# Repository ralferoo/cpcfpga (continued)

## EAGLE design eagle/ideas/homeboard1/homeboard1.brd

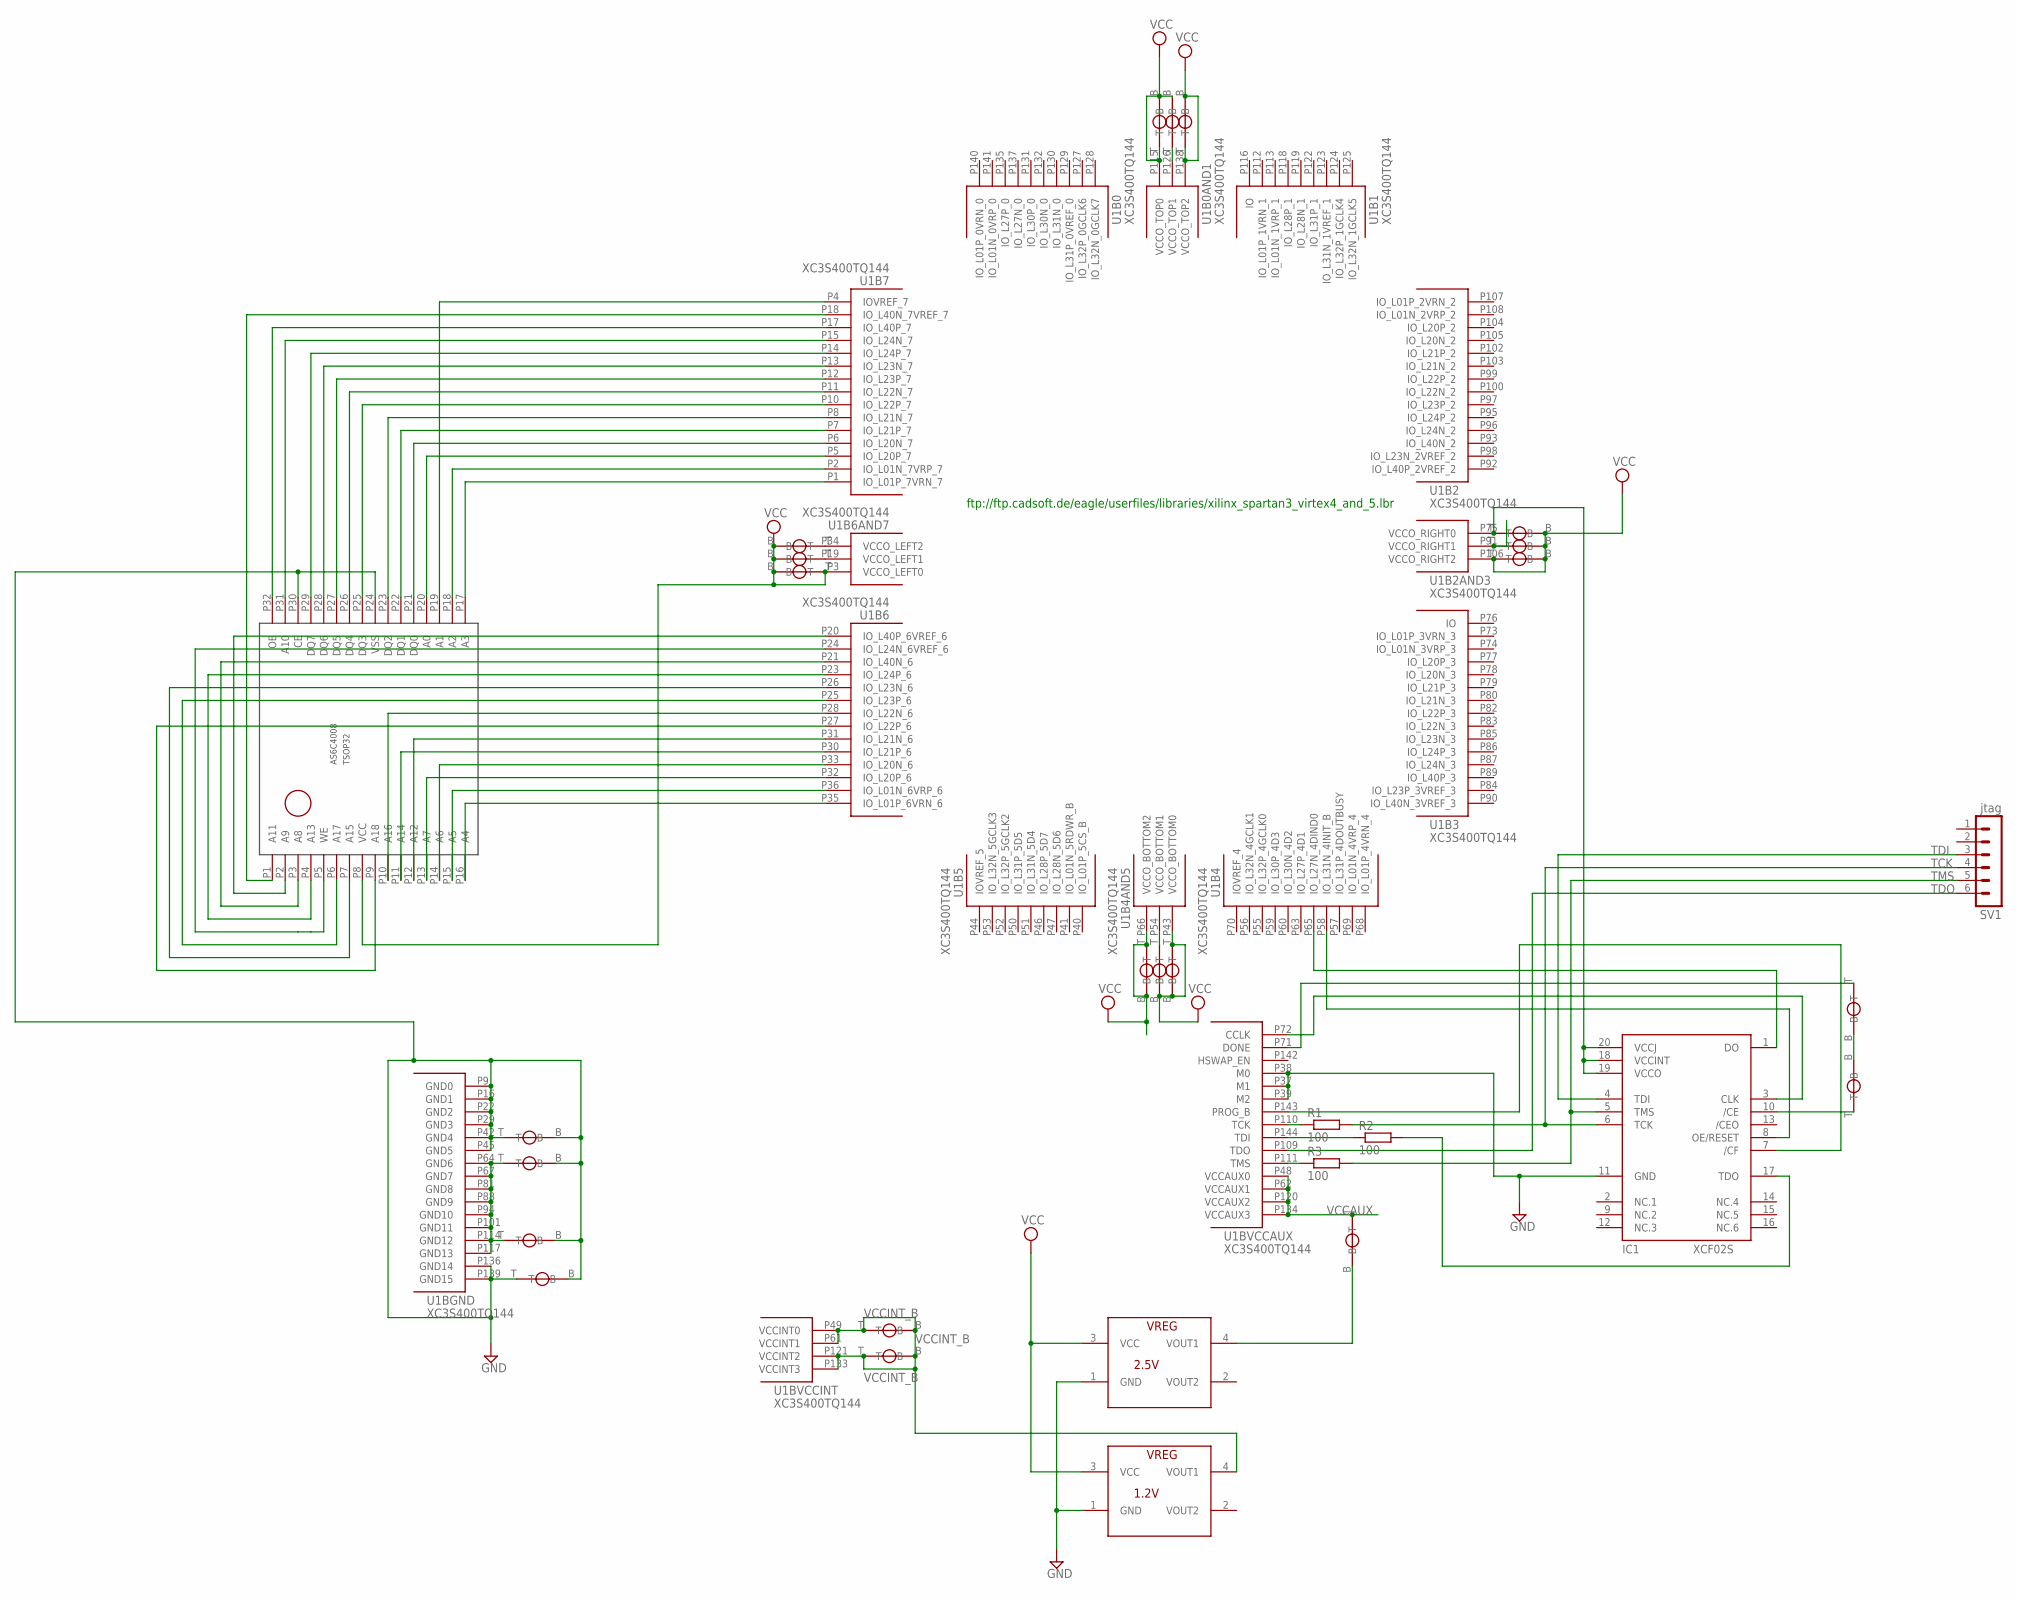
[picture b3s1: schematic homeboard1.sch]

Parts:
IC1: XCF02S; VO20
R1, R2, R3: 100; R0805
SV1: jtag; MA06-1
U1: XC3S400TQ144; TQ144
U$1, U$2, U$3, U$5, U$6, U$7, U$10, U$11, U$12, U$13, U$14, U$15, U$18, U$19, U$20, U$23, U$25, U$26, U$27, U$28, U$29: VIA_DIY
U$4: AS6C4008; TSOP32
U$8: 2.5V; SOT223
U$9: 1.2V; SOT223

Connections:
GND: IC1.11 (GND), U1.P9 (GND0), U1.P16 (GND1), U1.P22 (GND2), U1.P29 (GND3), U1.P37 (M1), U1.P38 (M0), U1.P39 (M2), U1.P42 (GND4), U1.P45 (GND5), U1.P136 (GND14), U1.P139 (GND15), U$2.B, U$3.B, U$3.T, U$4.P24 (VSS), U$4.P30 (CE), U$5.B, U$5.T, U$8.1 (GND), U$9.1 (GND), U$20.B
unnamed: U1.P1 (IO_L01P_7VRN_7), U$4.P17 (A3)
unnamed: U1.P2 (IO_L01N_7VRP_7), U$4.P18 (A2)
unnamed: U1.P126 (VCCO_TOP1), U$10.T
unnamed: U1.P64 (GND6), U1.P67 (GND7), U1.P81 (GND8), U1.P88 (GND9), U1.P94 (GND10), U1.P101 (GND11), U1.P114 (GND12), U1.P117 (GND13), U$2.T, U$20.T
unnamed: U1.P12 (IO_L23P_7), U$4.P27 (DQ5)
unnamed: U1.P13 (IO_L23N_7), U$4.P28 (DQ6)
unnamed: U1.P6 (IO_L20N_7), U$4.P21 (DQ0)
unnamed: R1.1, U1.P110 (TCK)
unnamed: IC1.1 (DO), U1.P65 (IO_L27N_4DIND0)
unnamed: U1.P7 (IO_L21P_7), U$4.P22 (DQ1)
unnamed: U1.P8 (IO_L21N_7), U$4.P23 (DQ2)
unnamed: R2.1, U1.P144 (TDI)
unnamed: IC1.17 (TDO), R2.2
unnamed: U1.P34 (VCCO_LEFT2), U$14.T
unnamed: U1.P19 (VCCO_LEFT1), U$15.T
unnamed: R3.1, U1.P111 (TMS)
unnamed: IC1.7 (/CF), U1.P143 (PROG_B)
unnamed: IC1.8 (OE/RESET), U1.P58 (IO_L31N_4INIT_B)
unnamed: IC1.3 (CLK), U1.P72 (CCLK)
unnamed: U1.P71 (DONE), U$13.T
unnamed: U1.P10 (IO_L22P_7), U$4.P25 (DQ3)
unnamed: U1.P11 (IO_L22N_7), U$4.P26 (DQ4)
unnamed: U1.P14 (IO_L24P_7), U$4.P29 (DQ7)
unnamed: U1.P54 (VCCO_BOTTOM1), U$25.T
unnamed: IC1.18 (VCCINT), IC1.19 (VCCO), IC1.20 (VCCJ), U1.P75 (VCCO_RIGHT0), U$29.T
unnamed: U1.P15 (IO_L24N_7), U$4.P31 (A10)
unnamed: U1.P91 (VCCO_RIGHT1), U$28.T
unnamed: U1.P17 (IO_L40P_7), U$4.P32 (OE)
unnamed: U1.P28 (IO_L22N_6), U$4.P10 (A16)
unnamed: U1.P30 (IO_L21P_6), U$4.P11 (A14)
unnamed: U1.P31 (IO_L21N_6), U$4.P12 (A12)
unnamed: U1.P20 (IO_L40P_6VREF_6), U$4.P2 (A9)
unnamed: U1.P32 (IO_L20P_6), U$4.P13 (A7)
unnamed: U1.P33 (IO_L20N_6), U$4.P14 (A6)
unnamed: U1.P27 (IO_L22P_6), U$4.P9 (A18)
unnamed: U1.P35 (IO_L01P_6VRN_6), U$4.P16 (A4)
unnamed: U1.P36 (IO_L01N_6VRP_6), U$4.P15 (A5)
unnamed: U$8.4 (VOUT1), U$11.B
unnamed: IC1.10 (/CE), U$12.T
unnamed: U$12.B, U$13.B
unnamed: U1.P5 (IO_L20P_7), U$4.P20 (A0)
unnamed: U1.P4 (IOVREF_7), U$4.P19 (A1)
unnamed: U1.P18 (IO_L40N_7VREF_7), U$4.P1 (A11)
unnamed: U1.P23 (IO_L24P_6), U$4.P4 (A13)
unnamed: U1.P21 (IO_L40N_6), U$4.P3 (A8)
unnamed: U1.P24 (IO_L24N_6VREF_6), U$4.P5 (WE)
unnamed: U1.P25 (IO_L23P_6), U$4.P6 (A17)
unnamed: U1.P26 (IO_L23N_6), U$4.P7 (A15)
TCK: IC1.6 (TCK), R1.2, SV1.4
TDI: IC1.4 (TDI), SV1.3
TDO: SV1.6, U1.P109 (TDO)
TMS: IC1.5 (TMS), R3.2, SV1.5
VCC: U1.P3 (VCCO_LEFT0), U1.P43 (VCCO_BOTTOM0), U1.P66 (VCCO_BOTTOM2), U1.P106 (VCCO_RIGHT2), U1.P115 (VCCO_TOP0), U1.P138 (VCCO_TOP2), U$4.P8 (VCC), U$6.B, U$6.T, U$7.B, U$7.T, U$8.3 (VCC), U$9.3 (VCC), U$10.B, U$14.B, U$15.B, U$18.B, U$18.T, U$19.B, U$19.T, U$25.B, U$26.B, U$26.T, U$27.B, U$27.T, U$28.B, U$29.B
VCCAUX: U1.P48 (VCCAUX0), U1.P62 (VCCAUX1), U1.P120 (VCCAUX2), U1.P134 (VCCAUX3), U$11.T
VCCINT_B: U1.P49 (VCCINT0), U1.P61 (VCCINT1), U1.P121 (VCCINT2), U1.P133 (VCCINT3), U$1.B, U$1.T, U$9.4 (VOUT1), U$23.B, U$23.T

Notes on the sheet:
ftp://ftp.cadsoft.de/eagle/userfiles/libraries/xilinx_spartan3_virtex4_and_5.lbr

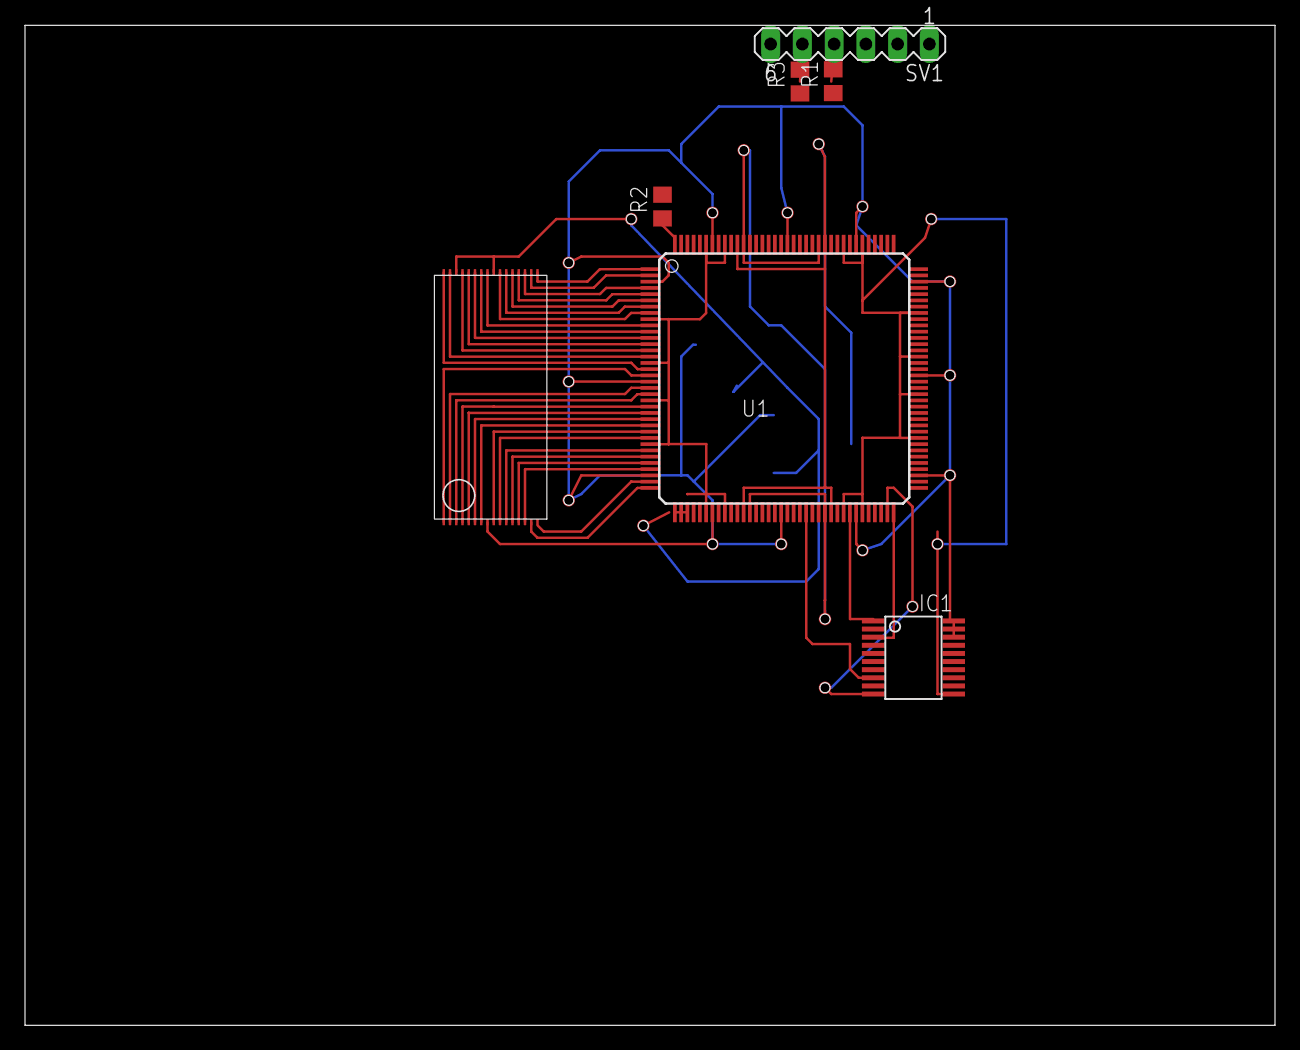
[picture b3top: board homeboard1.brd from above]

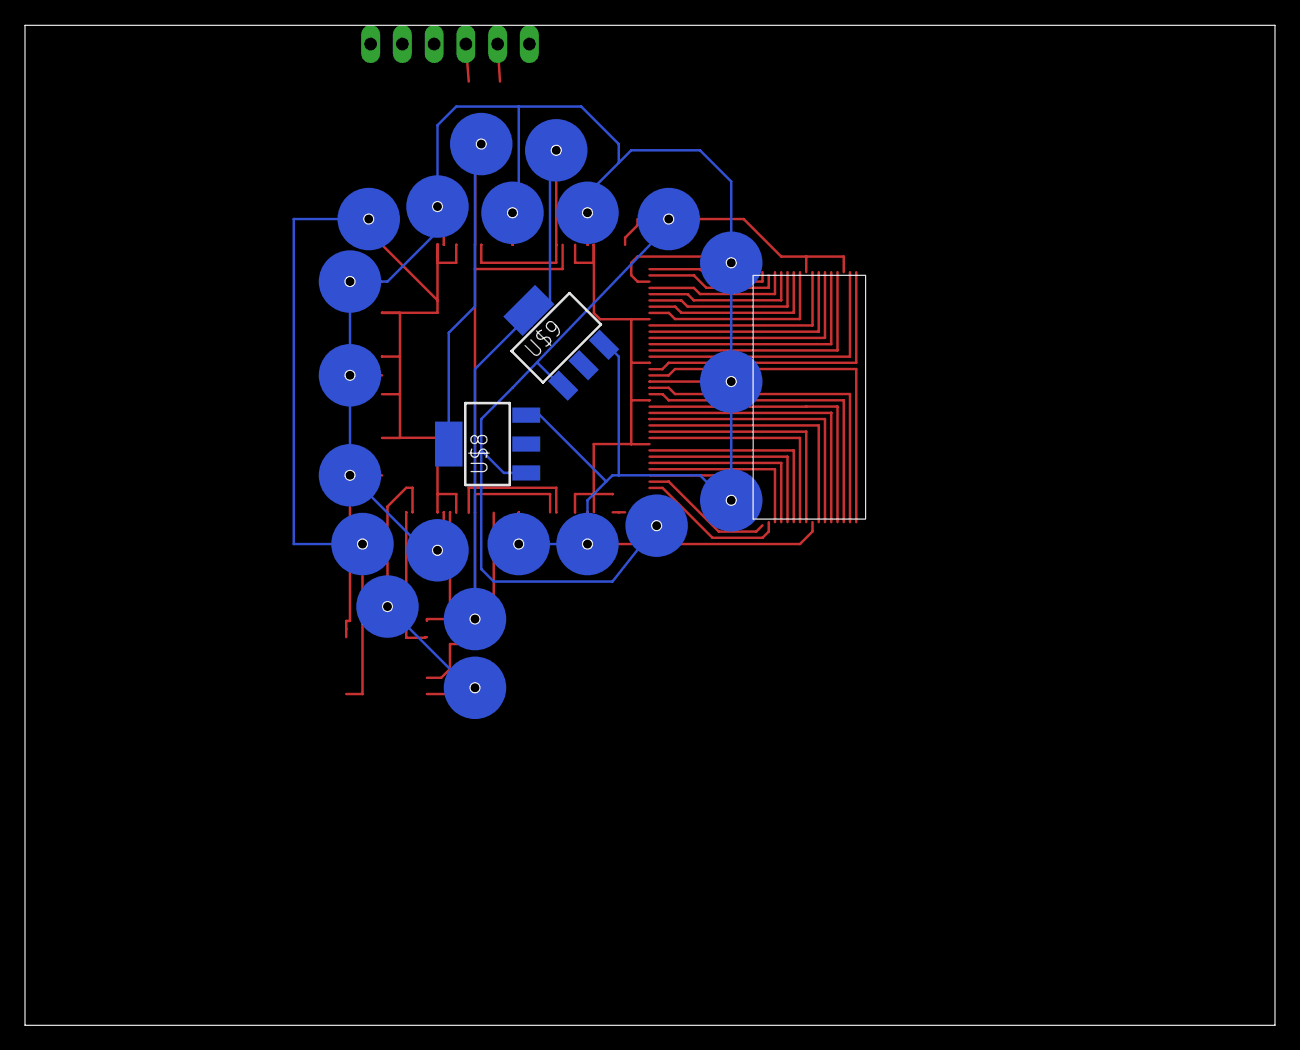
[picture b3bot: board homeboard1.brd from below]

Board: 2 copper layers, 100.0 x 80.0 mm, 30 parts (2 on the bottom side), 56 nets.

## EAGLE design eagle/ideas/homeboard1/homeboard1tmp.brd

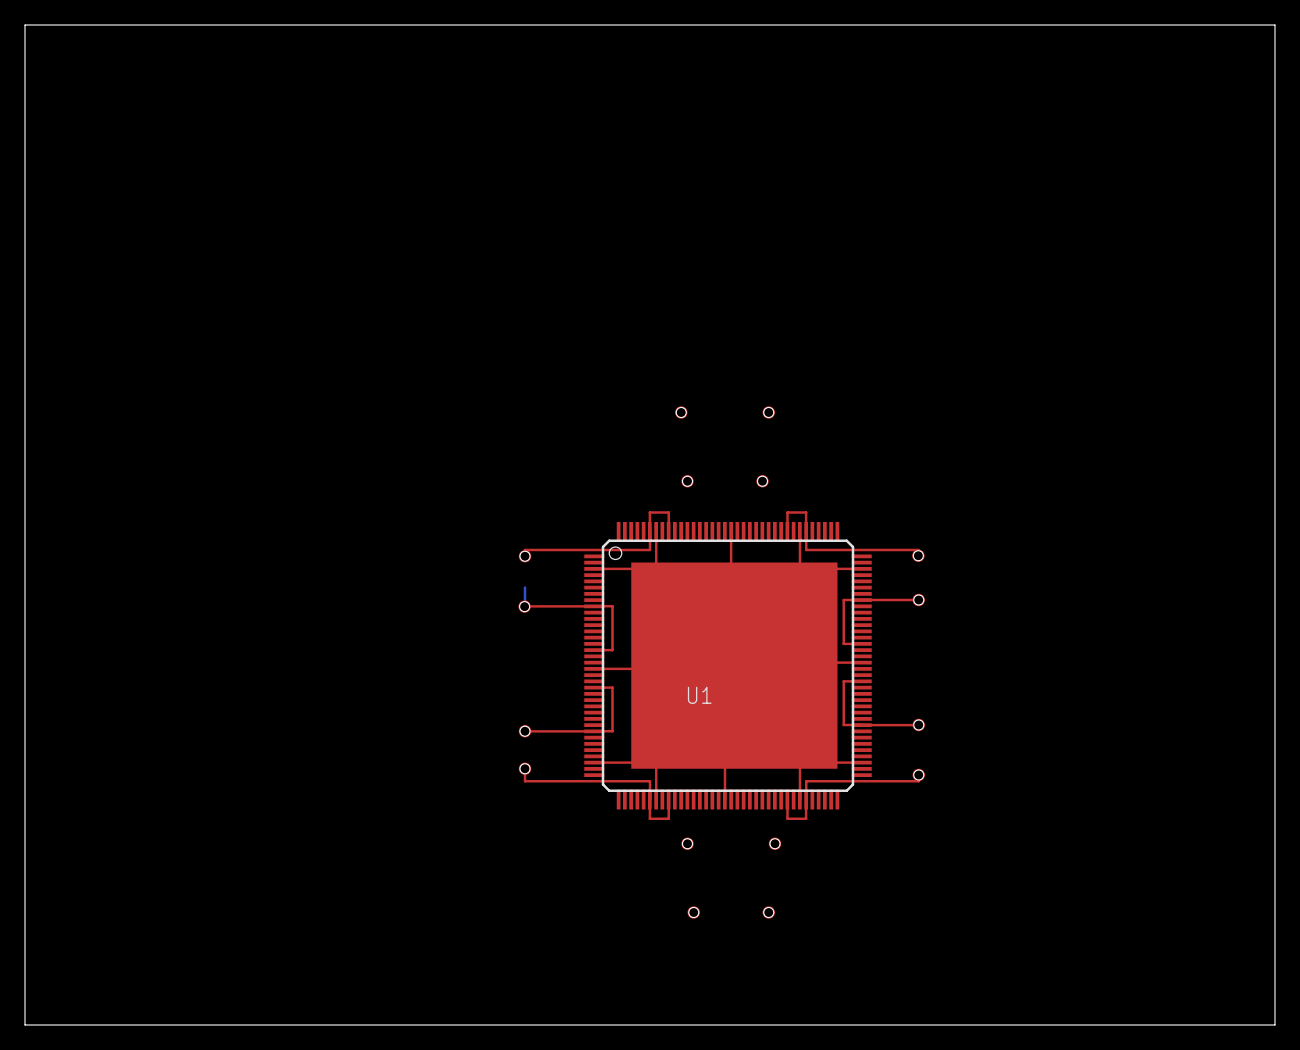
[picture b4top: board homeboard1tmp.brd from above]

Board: 2 copper layers, 100.0 x 80.0 mm, 17 parts (0 on the bottom side), 20 nets.

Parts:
U1: XC3S400TQ144; TQ144
U$1, U$2, U$3, U$4, U$5, U$8, U$9, U$12, U$13, U$16, U$17, U$20, U$21, U$22, U$23, U$24: VIA_DIY

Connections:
GND: U1.P136, U1.P139, U$20.T
GND_B: U$5.B, U$8.B, U$9.B, U$12.B, U$13.B, U$16.B, U$17.B, U$20.B
unnamed: U1.P9, U1.P16, U$5.T
unnamed: U1.P42, U1.P45, U$9.T
unnamed: U1.P22, U1.P29, U$8.T
unnamed: U1.P64, U1.P67, U$12.T
unnamed: U1.P81, U1.P88, U$13.T
unnamed: U1.P94, U1.P101, U$16.T
unnamed: U1.P114, U1.P117, U$17.T
unnamed: U1.P48, U$22.T
unnamed: U1.P133, U$24.T
unnamed: U1.P61, U$23.T
unnamed: U1.P134, U$21.T
unnamed: U$3.B, U$4.B, U$21.B, U$22.B
unnamed: U1.P62, U$3.T
VCC: U1.P3, U1.P19, U1.P34, U1.P43, U1.P54, U1.P66, U1.P75, U1.P91, U1.P106, U1.P115, U1.P126, U1.P138
VCCAUX: U1.P120, U$4.T
VCCINT01: U1.P49, U$1.T
VCCINT23: U1.P121, U$2.T
VCCINT_B: U$1.B, U$2.B, U$23.B, U$24.B
